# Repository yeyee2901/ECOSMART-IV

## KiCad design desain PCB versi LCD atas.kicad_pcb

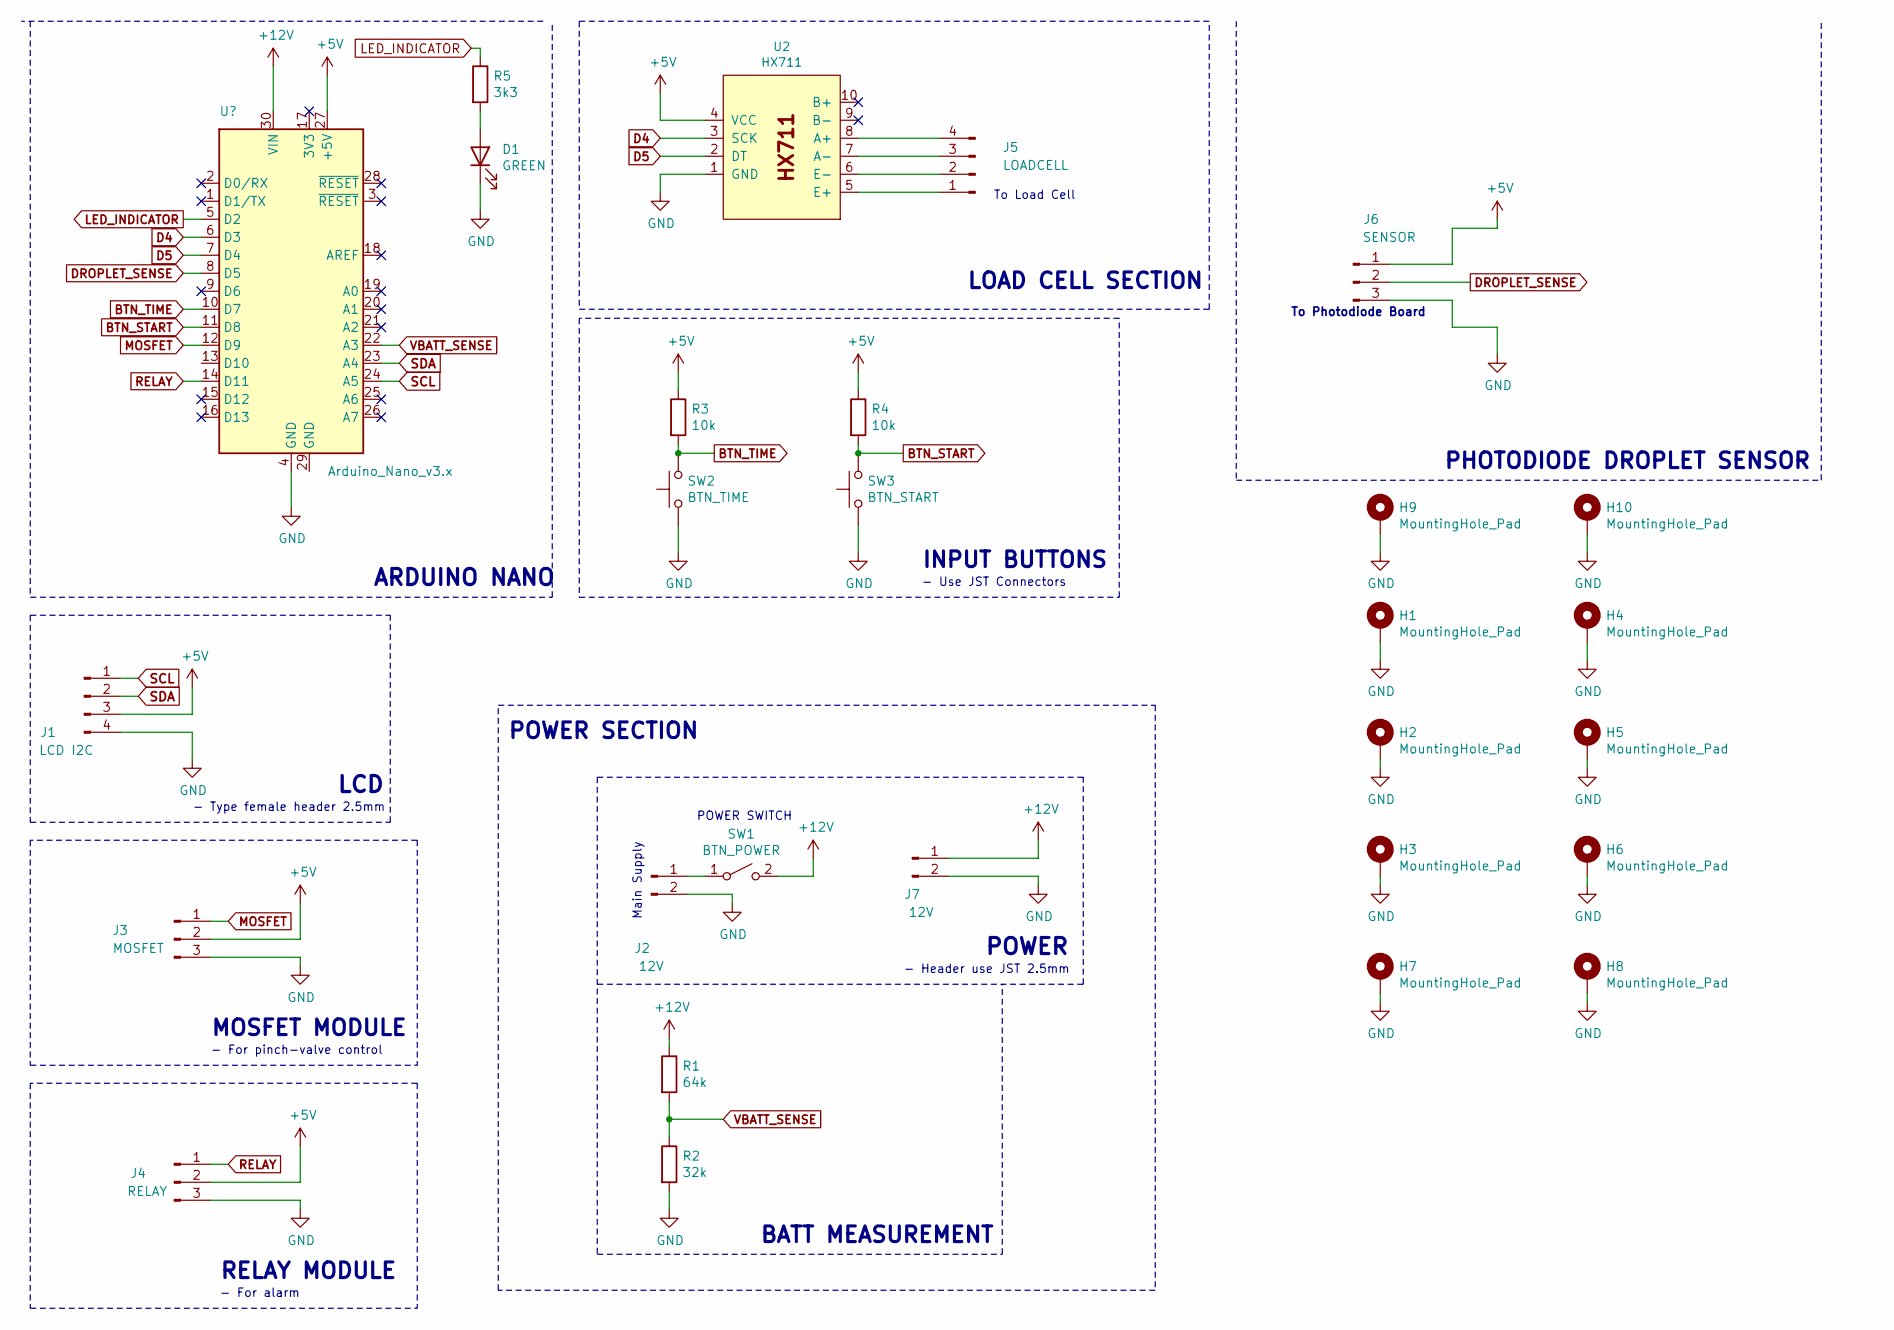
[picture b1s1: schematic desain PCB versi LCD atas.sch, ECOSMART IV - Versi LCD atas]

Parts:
D1: GREEN; LED_D3.0mm
H1, H2, H3, H4, H5, H6, H7, H8, H9, H10: MountingHole_Pad; MountingHole_3.2mm_M3_Pad
J1: LCD I2C; PinHeader_1x04_P2.54mm_Vertical
J2, J7: 12V; JST_EH_B2B-EH-A_1x02_P2.50mm_Vertical
J3: MOSFET; PinHeader_1x03_P2.54mm_Vertical
J4: RELAY; PinHeader_1x03_P2.54mm_Vertical
J5: LOADCELL; PinSocket_1x04_P2.54mm_Vertical
J6: SENSOR; PinSocket_1x03_P2.54mm_Vertical
R1: 64k; R_Axial_DIN0309_L9.0mm_D3.2mm_P15.24mm_Horizontal
R2: 32k; R_Axial_DIN0309_L9.0mm_D3.2mm_P15.24mm_Horizontal
R3, R4: 10k; R_Axial_DIN0309_L9.0mm_D3.2mm_P15.24mm_Horizontal
R5: 3k3; R_Axial_DIN0309_L9.0mm_D3.2mm_P15.24mm_Horizontal
SW1: BTN_POWER; JST_EH_B2B-EH-A_1x02_P2.50mm_Vertical
SW2: BTN_TIME; JST_EH_B2B-EH-A_1x02_P2.50mm_Vertical
SW3: BTN_START; JST_EH_B2B-EH-A_1x02_P2.50mm_Vertical
U2: HX711

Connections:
+5V: J1.3, J3.2, J4.2, J6.1, R3.1, R4.1, U2.4 (VCC); also elsewhere on the board
+12V: J7.1, R1.1, SW1.2 (B); also elsewhere on the board
BTN_START: R4.2, SW3.2; also elsewhere on the board
BTN_TIME: R3.2, SW2.2; also elsewhere on the board
D4: U2.3 (SCK); also elsewhere on the board
D5: U2.2 (DT); also elsewhere on the board
DROPLET_SENSE: J6.2; also elsewhere on the board
GND: D1.1 (K), H1.1, H2.1, H3.1, H4.1, H5.1, H6.1, H7.1, H8.1, H9.1, H10.1, J1.4, J2.2, J3.3, J4.3, J6.3, J7.2, R2.2, SW2.1, SW3.1, U2.1 (GND); also elsewhere on the board
LED_INDICATOR: R5.1; also elsewhere on the board
MOSFET: J3.1; also elsewhere on the board
unnamed: D1.2 (A), R5.2
unnamed: J2.1, SW1.1 (A)
unnamed: J5.1, U2.5 (E+)
unnamed: J5.2, U2.6 (E-)
unnamed: J5.3, U2.7 (A-)
unnamed: J5.4, U2.8 (A+)
RELAY: J4.1; also elsewhere on the board
SCL: J1.1; also elsewhere on the board
SDA: J1.2; also elsewhere on the board
VBATT_SENSE: R1.2, R2.1; also elsewhere on the board

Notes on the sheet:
LCD
ARDUINO NANO
- Type female header 2.5mm
LOAD CELL SECTION
To Load Cell
INPUT BUTTONS
- Use JST Connectors
PHOTODIODE DROPLET SENSOR
MOSFET MODULE
- For pinch-valve control
RELAY MODULE
- For alarm
BATT MEASUREMENT
Main Supply
- Header use JST 2.5mm
POWER SWITCH
POWER
POWER SECTION
To Photodiode Board

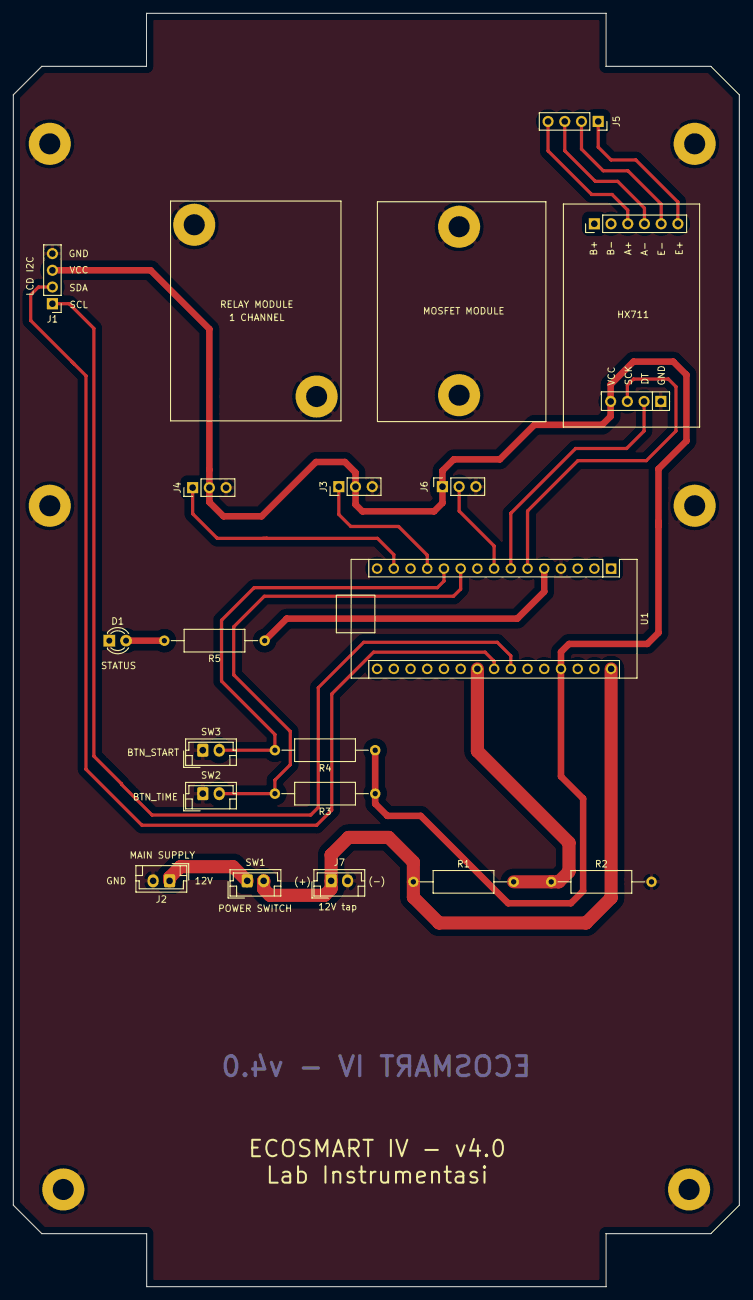
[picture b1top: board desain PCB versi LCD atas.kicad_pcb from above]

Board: 2 copper layers, 110.3 x 193.5 mm, 28 parts (0 on the bottom side), 20 nets.

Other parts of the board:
U1: Arduino_Nano_v3.x; Arduino_Nano

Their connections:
+5V: U1.27; also elsewhere on the board
+12V: U1.30; also elsewhere on the board
BTN_START: U1.11; also elsewhere on the board
BTN_TIME: U1.10; also elsewhere on the board
D4: U1.6; also elsewhere on the board
D5: U1.7; also elsewhere on the board
DROPLET_SENSE: U1.8; also elsewhere on the board
GND: U1.4; also elsewhere on the board
LED_INDICATOR: U1.5; also elsewhere on the board
MOSFET: U1.12; also elsewhere on the board
RELAY: U1.14; also elsewhere on the board
SCL: U1.24; also elsewhere on the board
SDA: U1.23; also elsewhere on the board
VBATT_SENSE: U1.22; also elsewhere on the board

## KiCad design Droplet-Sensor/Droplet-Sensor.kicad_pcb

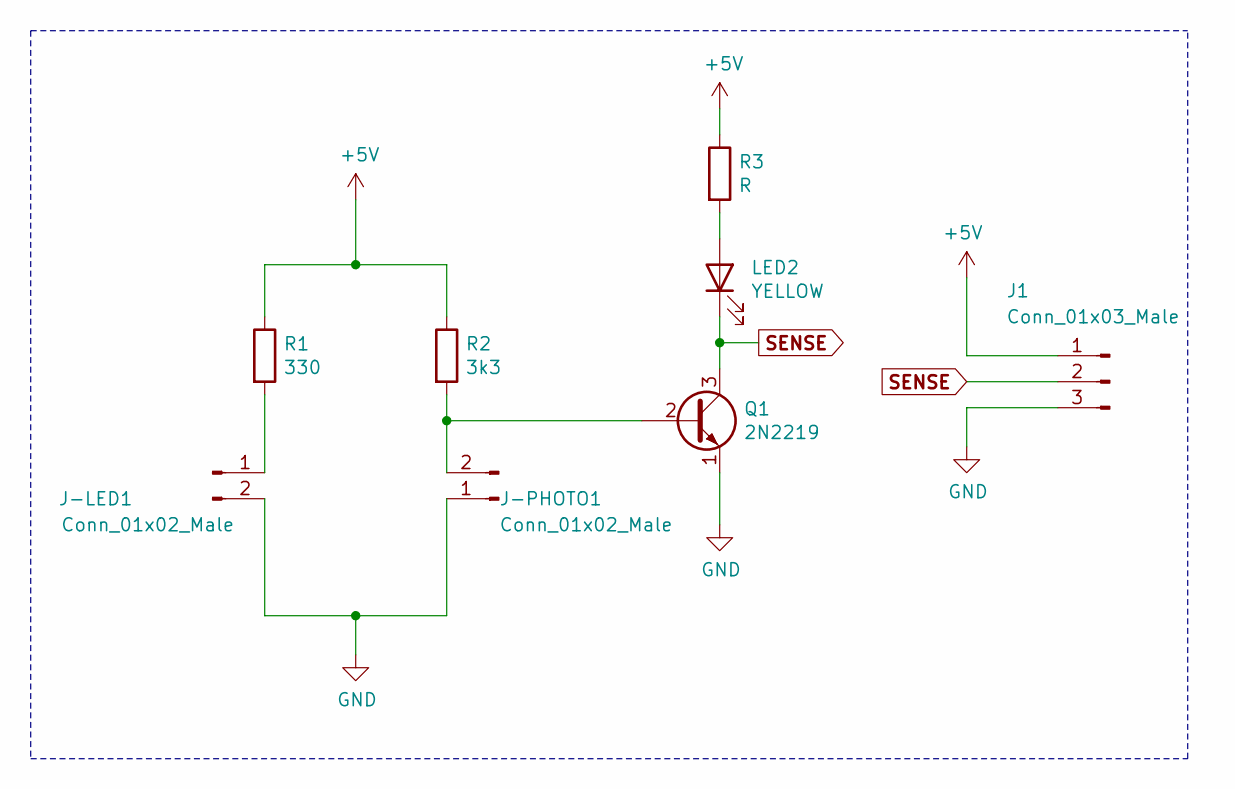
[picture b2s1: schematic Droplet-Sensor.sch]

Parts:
J1: Conn_01x03_Male; PinHeader_1x03_P2.00mm_Vertical
J-LED1: Conn_01x02_Male; JST_EH_B2B-EH-A_1x02_P2.50mm_Vertical
J-PHOTO1: Conn_01x02_Male; JST_EH_B2B-EH-A_1x02_P2.50mm_Vertical
LED2: YELLOW; LED_D3.0mm
Q1: 2N2219; TO-39-3
R1: 330; R_Axial_DIN0207_L6.3mm_D2.5mm_P15.24mm_Horizontal
R2: 3k3; R_Axial_DIN0207_L6.3mm_D2.5mm_P15.24mm_Horizontal
R3: R; R_Axial_DIN0207_L6.3mm_D2.5mm_P15.24mm_Horizontal

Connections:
+5V: J1.1, R1.1, R2.1, R3.1
GND: J1.3, J-LED1.2, J-PHOTO1.1, Q1.1 (E)
unnamed: J-LED1.1, R1.2
unnamed: J-PHOTO1.2, Q1.2 (B), R2.2
unnamed: LED2.2 (A), R3.2
SENSE: J1.2, LED2.1 (K), Q1.3 (C)

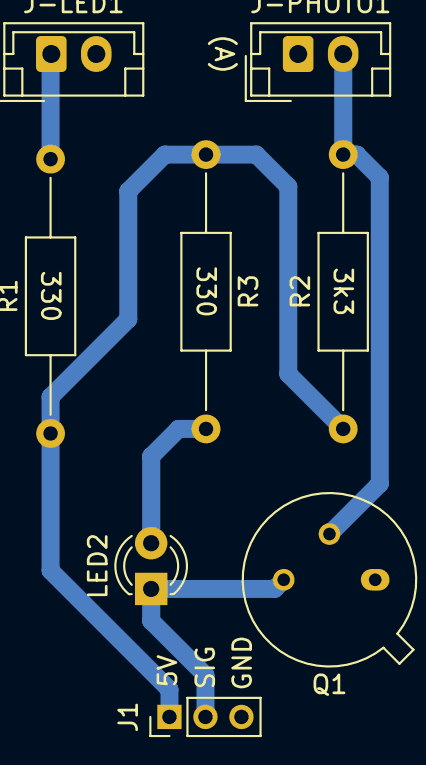
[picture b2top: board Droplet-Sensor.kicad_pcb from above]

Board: 2 copper layers, 8 parts (0 on the bottom side), 6 nets.

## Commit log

2021-11-01 Initial commit: trans to 1 layer only
